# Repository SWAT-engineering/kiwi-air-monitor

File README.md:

Kiwi air monitor is an open source CO2/Humidity/Temperature sensor intended for monitoring the indoor air quality. Kiwi air monitor was initiated by [swat.engineering](https://www.swat.engineering) to support teachers and school organizations with the ventilation of the class rooms. 

## Features

- Monitor CO2, Humidity, Temperature, Atmospheric Pressure 
- Display current measurements and its trend on a small display
- Blink a warning light if certain thresholds are reached (> 800ppm CO2 for example)
- Optionally: publish sensor readings to a (self hosted) MQTT server to allow building wide monitoring
- Optionally: partial remote control via MQTT
- Optionally: Updating firmware over wifi (OTA) 
- Optionally: Docker-compose based Dashboard & MQTT server setup

Due to the cost-cutting concern, we have focussed more on precision instead of accuracy. Meaning that if a value increases, it should indeed represent an increase in that property, but it is acceptable to have a bias with respect to more expensive measurements. So you might get a temperature of 20.4 degrees C even though it iss actually 20.9 degrees C but if it increases to 20.5 degrees C it indeed is now 21.0 degrees C.

## Hardware

The hardware is build around the ESP8266 platform. The costs (in the Netherlands) are roughly €45-50 per device. The list of components and schemas can be found in [doc/NL/Hardware.md](doc/NL/Hardware.md). We also provide a 3D model to print.

## Documentation
Please check out the documentation for further details and instructions about hardware and software, and user manuals:

1. [Dutch](doc/NL/)
2. [English](doc/ENG/) 

## Server

We've developed a small server setup (docker-compose based) so you can get started yourself. Checkout the [server/](server/) directory and the corresponding [documentation](docs/NL/Software.md).

## License

The software and 3D models are all [GPLv3 licensed](LICENSE). We use libraries with  compatible licenses. See [Software documentation](doc/NL/Software.md) for a list of which libraries are used.

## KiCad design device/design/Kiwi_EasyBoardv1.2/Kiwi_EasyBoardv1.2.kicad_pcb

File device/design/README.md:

# The Kiwi Monitor hardware

These are the design files for the version1.0 PCB of the Kiwi Air Monitor. The project has been designed using KiCad EDA.

All components can be "plugged" into the board on the female header connectors.

See the [../../doc/](../../doc/) folder for design documentation.

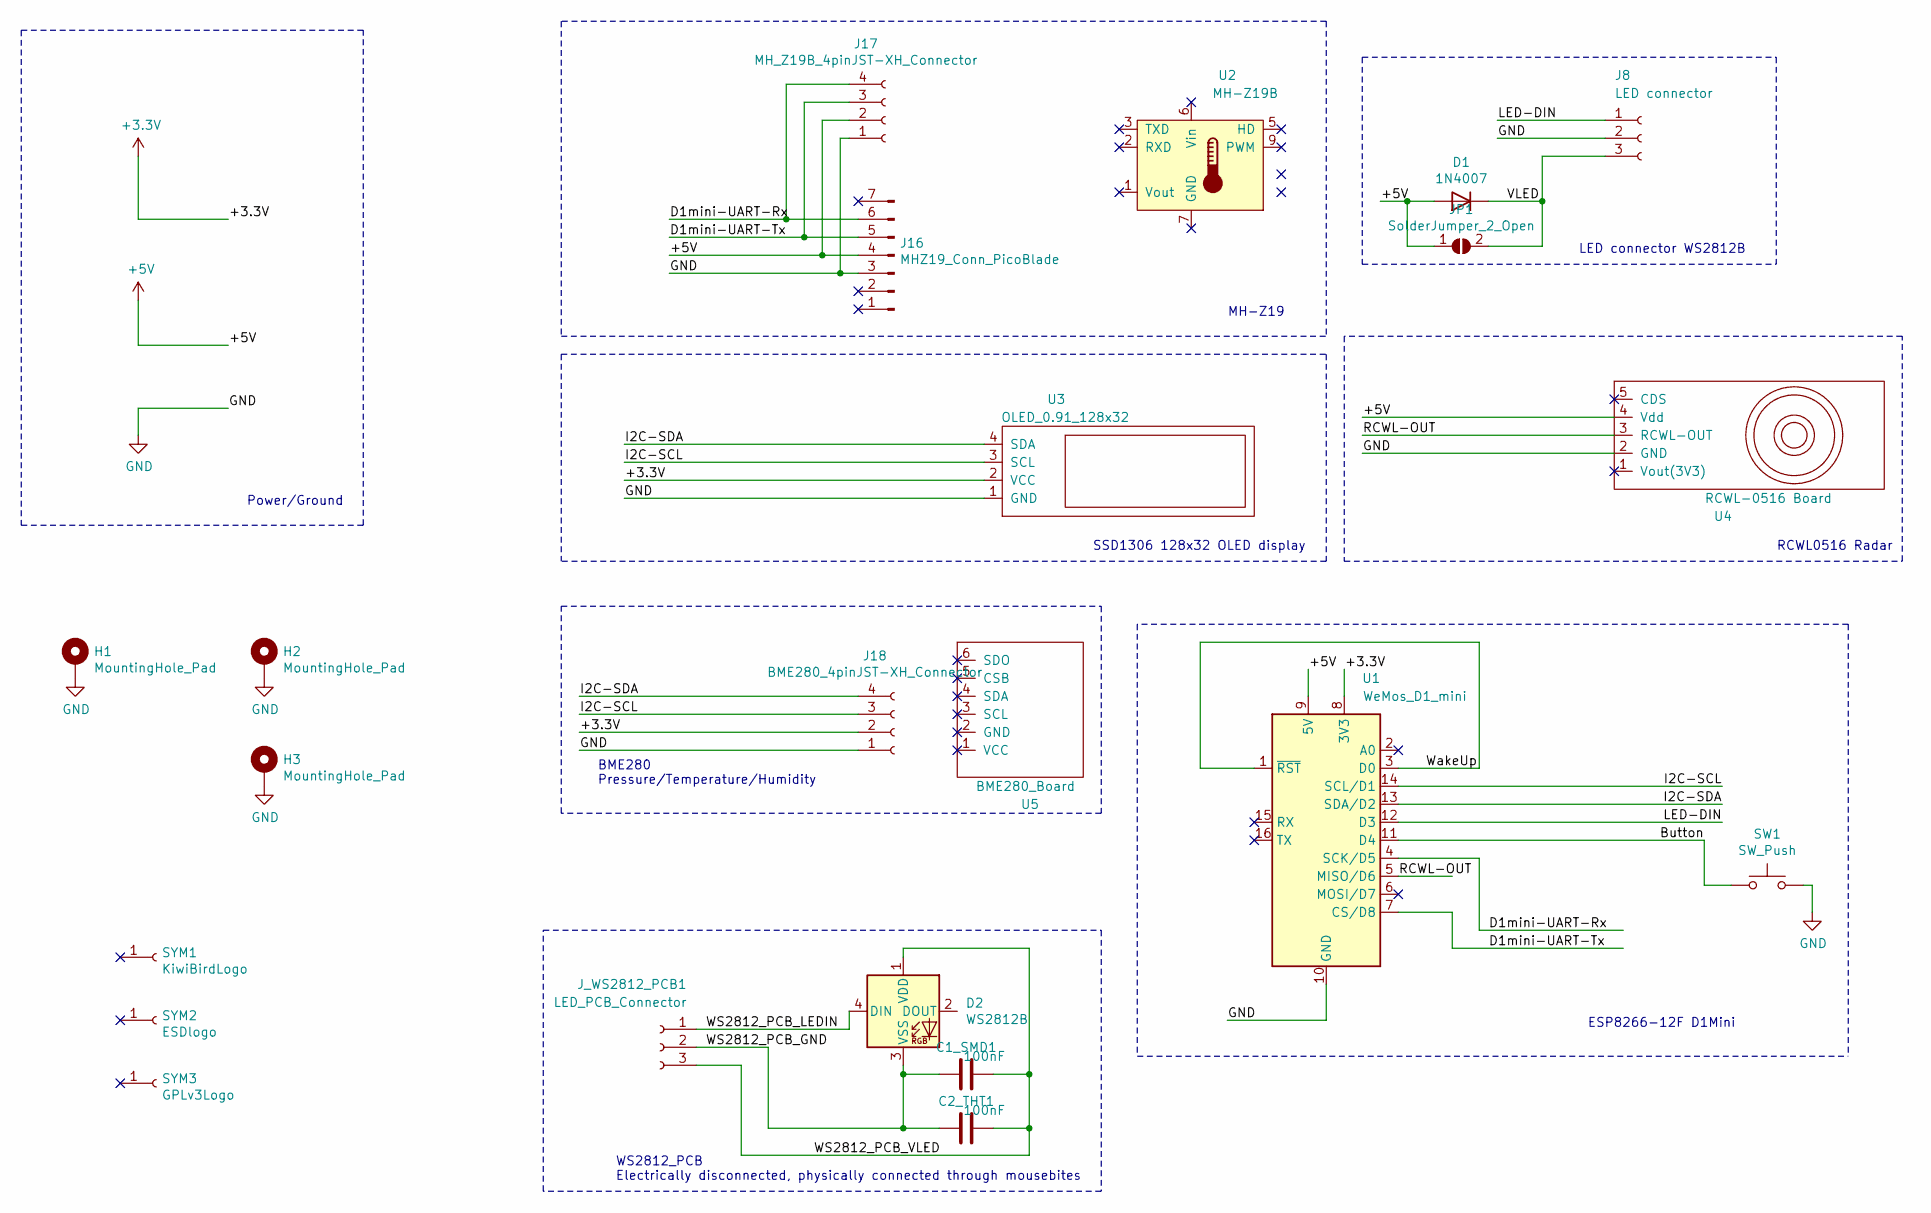
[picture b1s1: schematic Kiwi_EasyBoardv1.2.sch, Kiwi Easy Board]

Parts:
C1_SMD1: 100nF; C_0805_2012Metric_Pad1.18x1.45mm_HandSolder
C2_THT1: 100nF; C_Disc_D4.3mm_W1.9mm_P5.00mm
D1: 1N4007; D_DO-41_SOD81_P10.16mm_Horizontal
D2: WS2812B; LED_WS2812B_PLCC4_5.0x5.0mm_P3.2mm
H1, H2, H3: MountingHole_Pad; MountingHole_3.2mm_M3_Pad_TopBottom
J8: LED connector; JST_XH_B3B-XH-A_1x03_P2.50mm_Vertical
J16: MHZ19_Conn_PicoBlade; Molex_PicoBlade_53047-0710_1x07_P1.25mm_Vertical
J17: MH_Z19B_4pinJST-XH_Connector; JST_XH_B4B-XH-A_1x04_P2.50mm_Vertical
J18: BME280_4pinJST-XH_Connector; JST_XH_B4B-XH-A_1x04_P2.50mm_Vertical
JP1: SolderJumper_2_Open; SolderJumper-2_P1.3mm_Open_TrianglePad1.0x1.5mm
J_WS2812_PCB1: LED_PCB_Connector; PinHeader_1x03_P2.54mm_Vertical
SW1: SW_Push; SW_Tactile_Straight
SYM1: KiwiBirdLogo
SYM2: ESDlogo; ESD-Logo_8.9x8mm_SilkScreen
SYM3: GPLv3Logo; GPL3
U1: WeMos_D1_mini; WEMOS_D1_mini_light
U2: MH-Z19B; Winsen_MH-Z19B
U3: OLED_0.91_128x32
U4: RCWL-0516 Board; RCWL-0516
U5: BME280_Board

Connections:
+3V3: J18.2, U1.8 (3V3), U3.2 (VCC)
+5V: D1.2 (A), J16.4, J17.2, JP1.1 (A), U1.9 (5V), U4.4 (Vdd)
/Button: SW1.1, U1.11 (D4)
/D1mini-UART-Rx: J16.6, J17.4, U1.4 (SCK/D5)
/D1mini-UART-Tx: J16.5, J17.3, U1.7 (CS/D8)
/I2C-SCL: J18.3, U1.14 (SCL/D1), U3.3 (SCL)
/I2C-SDA: J18.4, U1.13 (SDA/D2), U3.4 (SDA)
/LED-DIN: J8.1, U1.12 (D3)
/RCWL-OUT: U1.5 (MISO/D6), U4.3 (RCWL-OUT)
/VLED: D1.1 (K), J8.3, JP1.2 (B)
/WS2812_PCB_GND: C1_SMD1.1, C2_THT1.1, D2.3 (VSS), J_WS2812_PCB1.2
/WS2812_PCB_LEDIN: D2.4 (DIN), J_WS2812_PCB1.1
/WS2812_PCB_VLED: C1_SMD1.2, C2_THT1.2, D2.1 (VDD), J_WS2812_PCB1.3
/WakeUp: U1.1 (~RST), U1.3 (D0)
GND: H1.1, H2.1, H3.1, J8.2, J16.3, J17.1, J18.1, SW1.2, U1.10 (GND), U3.1 (GND), U4.2 (GND)

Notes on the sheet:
MH-Z19
ESP8266-12F D1Mini
Power/Ground
SSD1306 128x32 OLED display
RCWL0516 Radar
LED connector WS2812B
BME280 Pressure/Temperature/Humidity
WS2812_PCB Electrically disconnected, physically connected through mousebites

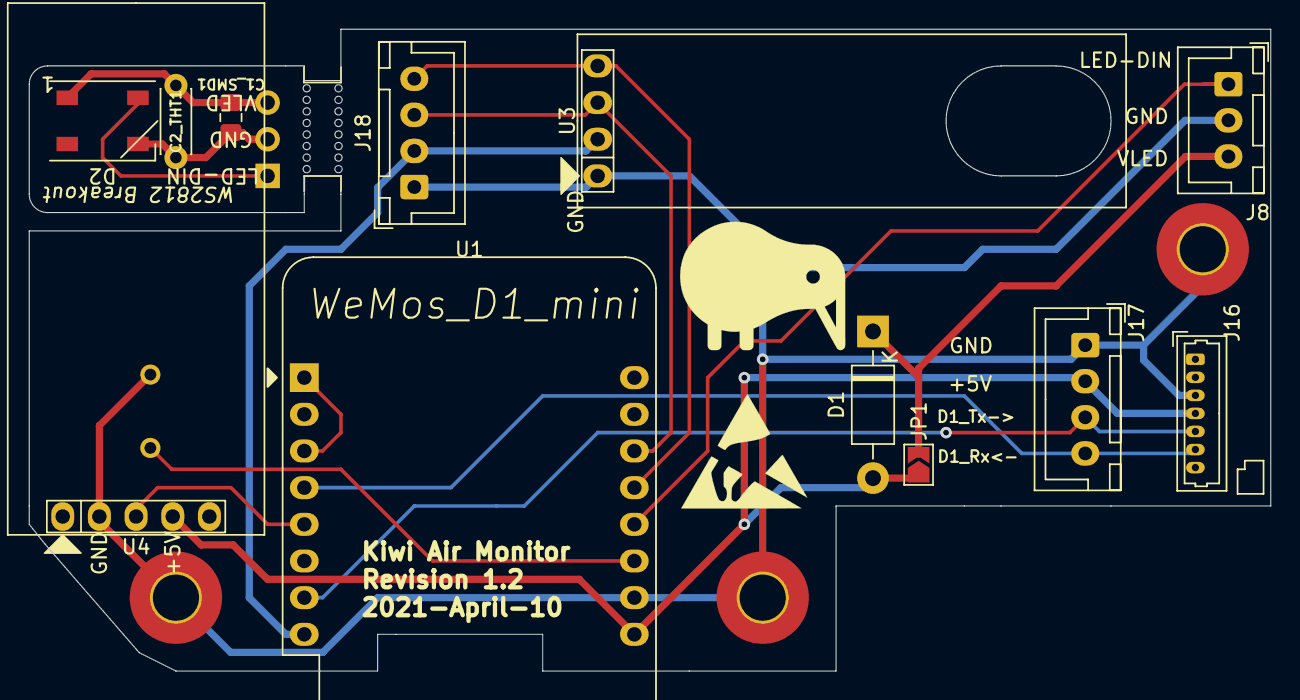
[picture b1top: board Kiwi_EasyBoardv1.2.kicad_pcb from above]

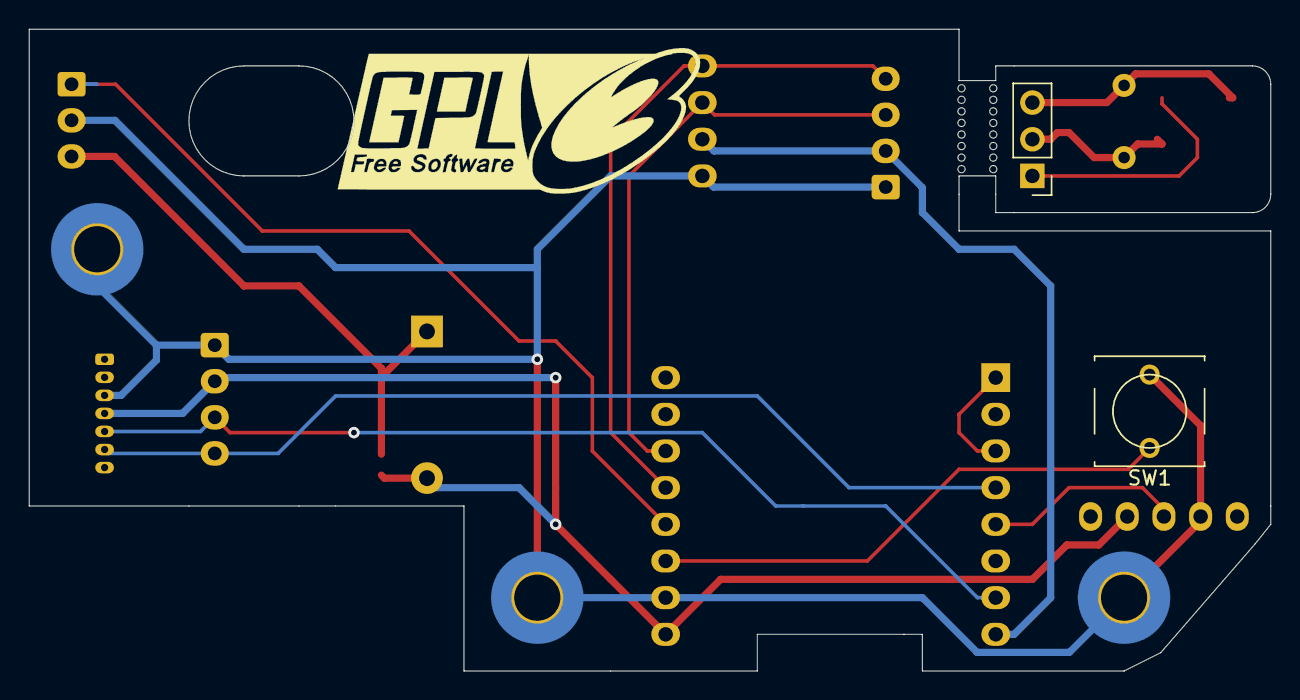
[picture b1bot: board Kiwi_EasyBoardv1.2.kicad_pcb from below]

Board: 2 copper layers, 86.0 x 44.5 mm, 21 parts (3 on the bottom side), 15 nets.

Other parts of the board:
mouse-bite-2.54mm-slot: VAL**; mouse-bite-2.54mm-slot

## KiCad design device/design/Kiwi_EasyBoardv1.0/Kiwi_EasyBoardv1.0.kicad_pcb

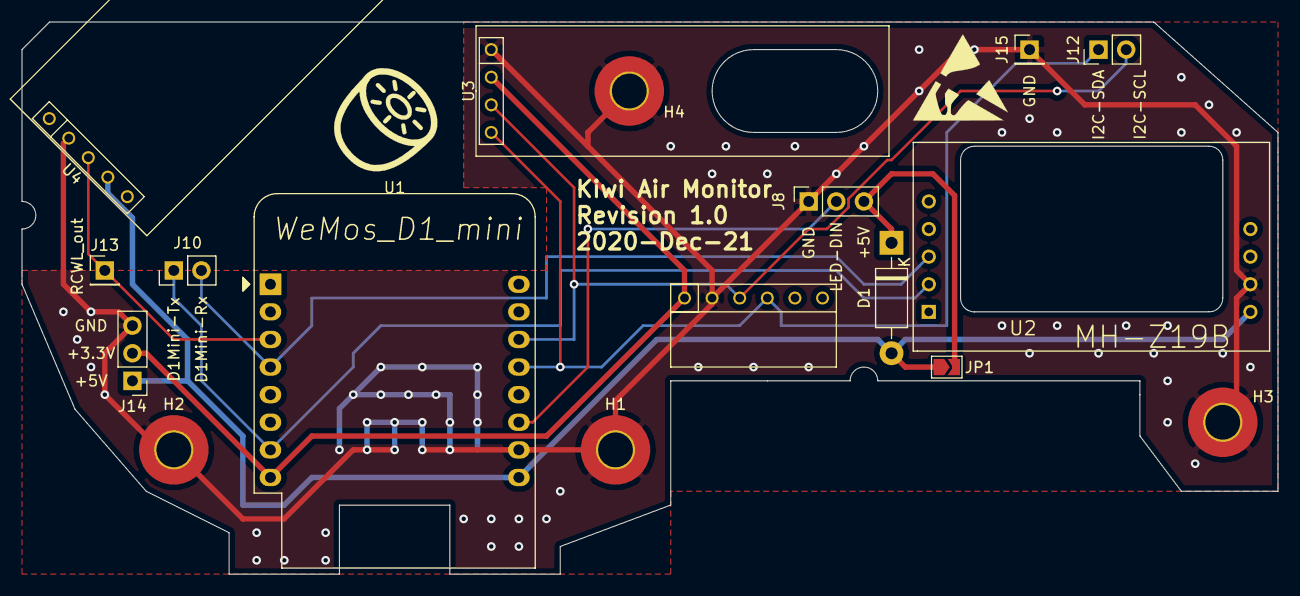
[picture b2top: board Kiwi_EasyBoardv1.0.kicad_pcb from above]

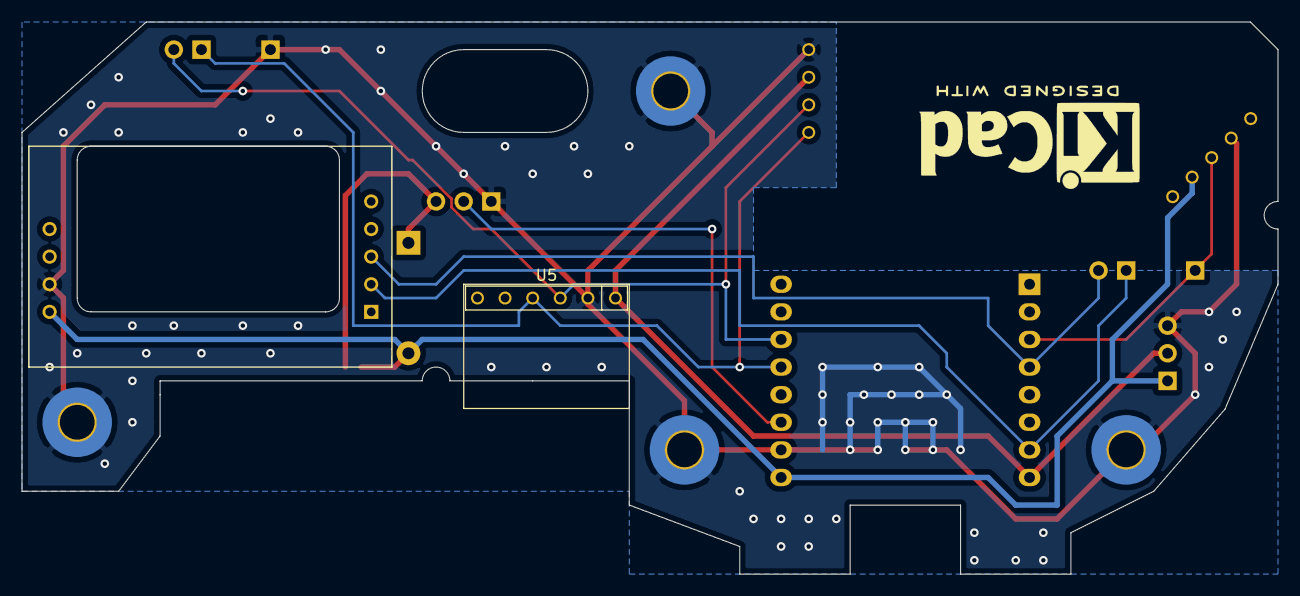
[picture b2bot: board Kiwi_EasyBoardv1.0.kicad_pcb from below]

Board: 2 copper layers, 115.6 x 50.8 mm, 18 parts (2 on the bottom side), 10 nets.

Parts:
D1: 1N4007; D_DO-41_SOD81_P10.16mm_Horizontal
GKiwi: LOGO; KiwiLogo
H1, H2, H3, H4: MountingHole_Pad; MountingHole_3.2mm_M3_Pad_TopBottom
J8: LED connector; PinSocket_1x03_P2.54mm_Vertical
J10: Conn_D1Mini_UART; PinHeader_1x02_P2.54mm_Vertical
J12: Conn_D1Mini_I2C; PinHeader_1x02_P2.54mm_Vertical
J13: Conn_RCWL_Out; PinHeader_1x01_P2.54mm_Vertical
J14: Conn_Power; PinHeader_1x03_P2.54mm_Vertical
J15: Conn_Ground; PinHeader_1x01_P2.54mm_Vertical
JP1: SolderJumper_2_Open; SolderJumper-2_P1.3mm_Open_TrianglePad1.0x1.5mm
U1: WeMos_D1_mini; WEMOS_D1_mini_light
U2: MH-Z19B; MH-Z19
U3: OLED_0.91_128x32
U4: RCWL-0516 Board; RCWL-0516
U5: BME280_Board

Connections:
+3V3: J14.2, U1.8, U3.2, U5.1
+5V: D1.2, J14.1, JP1.1, U1.9, U2.6, U4.4
/D1mini-UART-Rx: J10.2, U1.4, U2.3
/D1mini-UART-Tx: J10.1, U1.7, U2.2
/I2C-SCL: J12.2, U1.14, U3.3, U5.3
/I2C-SDA: J12.1, U1.13, U3.4, U5.4
/LED-DIN: J8.2, U1.11
/RCWL-OUT: J13.1, U1.3, U4.3
/VLED: D1.1, J8.3, JP1.2
GND: H1.1, H2.1, H3.1, H4.1, J8.1, J14.3, J15.1, U1.10, U2.7, U3.1, U4.2, U5.2

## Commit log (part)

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2020-10-13 Added some loos structure to the project
2020-10-15 Started with initial prototypes
2020-10-16 Imported MHZ19 sensor implementation from EspEasy
2020-10-16 Started writing new sensor framework with smoothing
2020-10-16 Switched BME sensors to sensor package
2020-10-16 Removing MH-Z19 package
2020-10-16 For now turn off sensor reset
2020-10-17 Better operation of the bme280 sensor
2020-10-17 Switching back to normal mh-z19 library
2020-10-18 Started moving screen logic to own class
2020-10-19 Rewrote all the logic out of the main class
2020-10-19 Cleanup of non needed code
2020-10-19 Wrote first version of hardware list
2020-10-20 Fixed small duplicate line in table
2020-10-20 Wrote hardware documentation and initial readme
2020-10-20 Added logo to bootscreen
2020-10-20 Added a bit more documentation about requirements
2020-10-20 Improved logo a bit
2020-10-20 Added costs remark about the sensor
2020-10-23 Fixed component
2020-10-23 Updated logo a bit
2020-10-23 Wrote generator to simulate a running kiwi monitor
    Fixes #17
2020-10-23 Wrote small docker compose file to get mosquitto and friends up and running
2020-10-24 Fixed some aspects of the generator
2020-10-24 Added a bit of readme for the server side
2020-10-25 Added support for rcwl sensor in code
2020-10-25 Switching more and more to timers
2020-10-25 Added RCWL sensor to build list
2020-10-26 Improved how the movement detection sensor works
2020-10-26 Revert "Cleanup of non needed code"
    This reverts commit 93ddd89a2f104734ef462590b8b2f650887b3b51.
2020-10-26 Switching back to the ESP easy based sensor fixes #22
2020-10-26 Updated wiring diagram to fit the PIR sensor
    resolves #6
2020-10-26 Added a way to mark failing sensors, to avoid it keep repeating the old value
    Resolves #21
2020-10-27 Temporarily importing arduino timer code, untill the new version is published at pio
2020-10-27 Extracting logic of WIFI and mqtt from the output component
2020-10-27 Added subscriptions to the mqtt connection
2020-10-28 Fixed includes for timer
2020-10-28 Fixed wifi setup
2020-10-29 Updated arduino-timer clone
2020-10-29 Implemented OTA updates via mqtt
2020-10-31 Added signing to the OTA updates
2020-10-31 Updated arduino-timer to 2.1.1 release untill on pio
2020-10-31 Added kiwi dashboard by default to grafana
2020-11-01 Updated the dashboard provisioning a bit, some manual work to allow users to change it more easily
2020-11-01 Switched display to timer code
2020-11-01 Improved timer code with the define
2020-11-03 add mqtt-2-influx
2020-11-03 correct typo
2020-11-03 add mqtt-2-influx to compose file
2020-11-03 change to network internal URLs
2020-11-03 correct influx insert
2020-11-03 add more tags
2020-11-04 add name to client config
2020-11-04 work on error messages
2020-11-04 don't put quotes around int and float
2020-11-04 only read client data once
2020-11-04 only unmarshal once
2020-11-04 put client in map and forward all errors to main
2020-11-06 move subscription to main
2020-11-06 remove handle functions
2020-11-06 adjust error msgs
2020-11-06 Switch display to always show all values and plot latest half hour, except if no movement detected
2020-11-06 Also publish voltage to the server, so we can track power loss
2020-11-06 Added first version of thresholds
2020-11-06 Moved all output related code to a single class to be initialized from main
2020-11-08 add dutch docs
2020-11-08 add readme
2020-11-10 respond to comments
2020-11-10 provide clients toml in volume and minor changes
2020-11-10 Update docs NL en hoofd readme gebaseerd op info die al aanwezig was.
2020-11-11 add server config to toml
2020-11-11 Improved how we measure co2
2020-11-11 Display and led improvements
2020-11-12 excape quotes and other changes
2020-11-12 move defer
2020-11-15 Tuning the PIR a bit more
2020-11-15 Added lots of details to the doc folder
2020-11-15 Made the readme more compact
2020-11-15 Added picture to readme
2020-11-16 Switch to multistage build and multiarch
2020-11-16 Updated imagename
2020-11-17 Build on native platform using cross compilation of golang
2020-11-17 Rewrote some stuff about design and switch the main chip
2020-11-20 Started with configuration tool
2020-11-21 Added calibrate code for 4 co2 sensors in one round
2020-11-23 Fixes to the calibration tool
2020-11-23 Working on the config tool
2020-11-25 Tweaked what we show in the display
2020-11-25 Added control of display in the mqtt bridge
2020-11-25 Added signing OTA files
2020-11-30 Fixed choppy eye timer
2020-11-30 Wrote how to make the cable for the co2 sensor
2020-12-03 Added mqtts support to generator
2020-12-03 Fixed tls 2nd time
2020-12-07 Fixed port setup
2020-12-12 Added a bit more debugging
2020-12-12 Added TLS support to the mqtt-2-influx (part of #31)
2020-12-13 Added ssl support to the mqtt forwarder
2020-12-13 Added better escaping of values to influx side
2020-12-13 Last fixes to get the status line correctly setup and error detection fixed
2020-12-13 Updated docker-compose config
2020-12-25 Added monitor version to try and compare multiple co2 ssensors at once
2020-12-29 Corrected the link to ../../doc
2020-12-29 Correction on Readme
2020-12-29 Added template for user config
2021-01-16 Latest changes to the co2 calibration code
2021-01-16 Implemented co2 sensor code based on wifwafs library
2021-01-24 Created directory structure for EasyBoardv1.0 and v1.1
2021-01-26 Removing remainders of calibration
2021-01-26 Also updated manuals to remove calibration section
2021-01-26 Removed final comment related to old sensor library
2021-01-27 Moved LED to D3 to avoid blue flickering light in the wemos
2021-01-29 Update the Hardware manual, added the step files, and the solderhelper
2021-02-22 Only publish every 60s
2021-02-22 Added support for disabling WiFi and multiple WiFi configs
2021-03-07 Correct 400 to 415, since sadly outside is not 400 anymore
2021-03-10 Increased brightness
2021-04-01 Improved display rendering
    - If no presence sensor detected and CO2 has been below 550 for a long time, don't render
    - Print mac address and connection status at startup for easy debugging (fix #38)
2021-04-21 Hardware design files of the board version 1.2
2021-05-11 Updated new port for the RCWL sensor on the new PCB
2021-06-17 Fixed error for disabled mqtt
2021-06-22 Made sure to always show the screen the first window of the movement
2021-10-05 Fix #41
2021-10-12 added config instructions to software.md
    added instructions about user-config.h to software.md
2021-12-13 Tuning of led for more yellow look on warning
2022-01-10 Trying better hostname
2022-01-29 Fixed hostname setup
2022-01-29 Allowed configuration of RCWL sensor sensitivity
2022-01-29 Render display more often to improve snappyness of the movement sensor based sleep
2022-01-31 Avoid recalculating the checksum of the image every 10 seconds
2022-02-02 Report firmware version more often
2022-07-01 Fix minor typo's in hardware.md
    Ik was hier toch toevallig (wil eindelijk dit eens gaan bouwen) en corrigeerde twee typefoutjes :)
2024-04-23 Bump golang.org/x/net in /server/generator
    Bumps [golang.org/x/net](https://github.com/golang/net) from 0.0.0-20201022231255-08b38378de70 to 0.23.0.
    - [Commits](https://github.com/golang/net/commits/v0.23.0)
    ---
    updated-dependencies:
    - dependency-name: golang.org/x/net
    dependency-type: indirect
2024-04-23 Bump golang.org/x/net in /server/generator (#44)
    Bumps [golang.org/x/net](https://github.com/golang/net) from 0.0.0-20201022231255-08b38378de70 to 0.23.0.
    - [Commits](https://github.com/golang/net/commits/v0.23.0)
    ---
    updated-dependencies:
    - dependency-name: golang.org/x/net
    dependency-type: indirect
2025-03-12 Bump golang.org/x/net from 0.23.0 to 0.36.0 in /server/generator
    Bumps [golang.org/x/net](https://github.com/golang/net) from 0.23.0 to 0.36.0.
    - [Commits](https://github.com/golang/net/compare/v0.23.0...v0.36.0)
    ---
    updated-dependencies:
    - dependency-name: golang.org/x/net
    dependency-type: indirect
2025-04-16 Bump golang.org/x/net from 0.23.0 to 0.38.0 in /server/generator
    Bumps [golang.org/x/net](https://github.com/golang/net) from 0.23.0 to 0.38.0.
    - [Commits](https://github.com/golang/net/compare/v0.23.0...v0.38.0)
    ---
    updated-dependencies:
    - dependency-name: golang.org/x/net
    dependency-version: 0.38.0
2025-12-02 Bump github.com/eclipse/paho.mqtt.golang in /server/generator
    Bumps [github.com/eclipse/paho.mqtt.golang](https://github.com/eclipse/paho.mqtt.golang) from 1.2.0 to 1.5.1.
    - [Release notes](https://github.com/eclipse/paho.mqtt.golang/releases)
    - [Commits](https://github.com/eclipse/paho.mqtt.golang/compare/v1.2.0...v1.5.1)
    ---
    updated-dependencies:
    - dependency-name: github.com/eclipse/paho.mqtt.golang
2025-12-02 Bump github.com/eclipse/paho.mqtt.golang in /server/generator (#49)
    Bumps [github.com/eclipse/paho.mqtt.golang](https://github.com/eclipse/paho.mqtt.golang) from 1.2.0 to 1.5.1.
    - [Release notes](https://github.com/eclipse/paho.mqtt.golang/releases)
    - [Commits](https://github.com/eclipse/paho.mqtt.golang/compare/v1.2.0...v1.5.1)
    ---
    updated-dependencies:
    - dependency-name: github.com/eclipse/paho.mqtt.golang
